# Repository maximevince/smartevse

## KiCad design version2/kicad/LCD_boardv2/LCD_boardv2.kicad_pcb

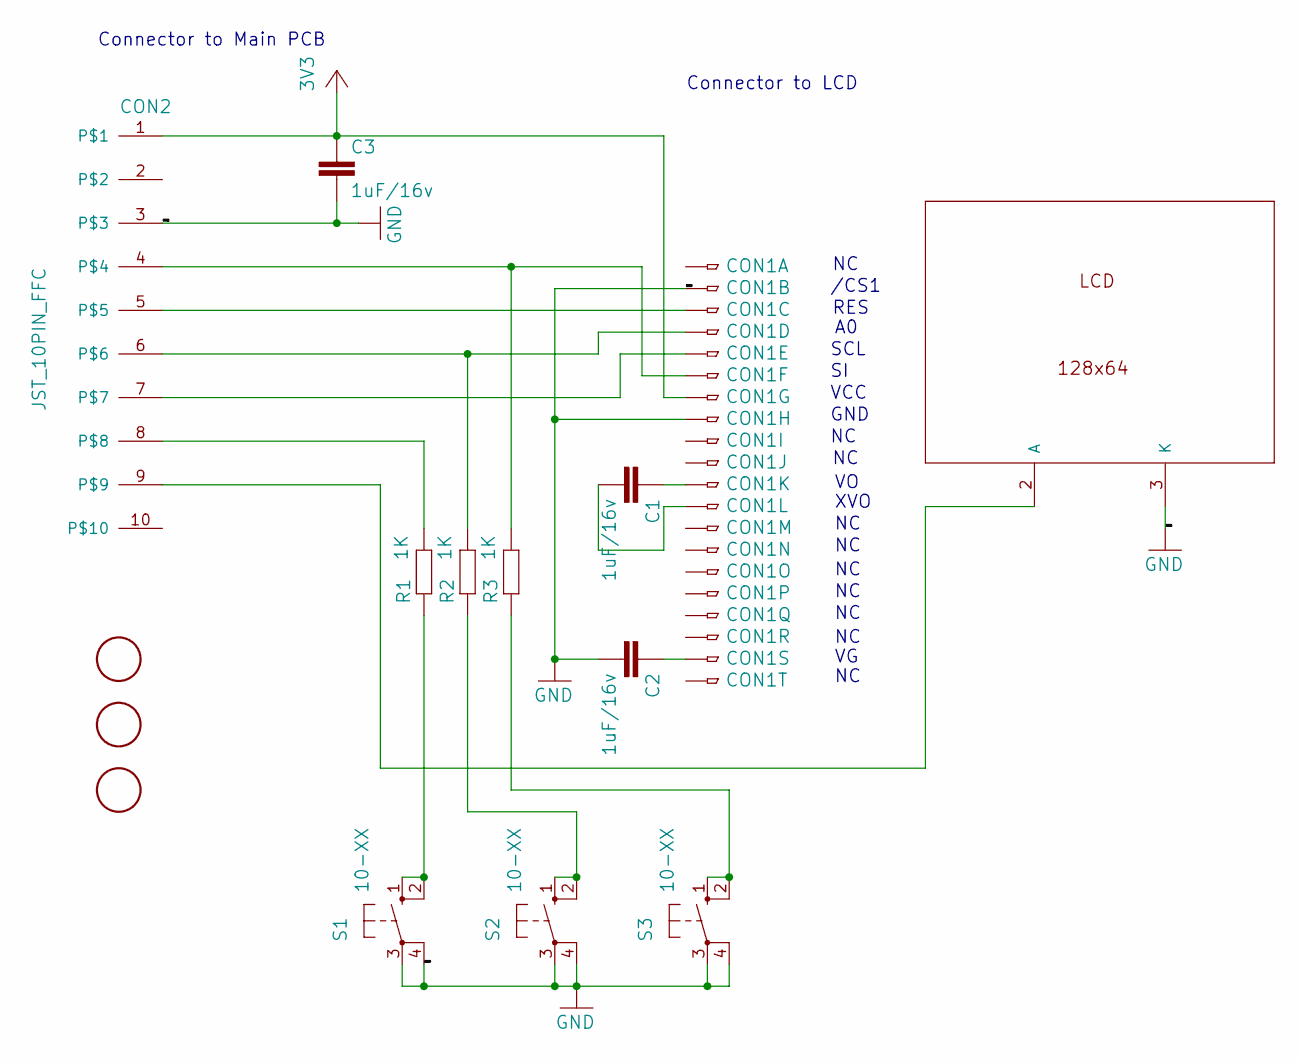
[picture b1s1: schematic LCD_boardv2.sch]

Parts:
C1, C2, C3: 1uF/16v; C0805
CON1: FH12-20S-0.5SH
CON2: JST_10PIN_FFC
R1, R2, R3: 1K; R0603
S1, S2, S3: 10-XX; B3F-10XX
U$1: LCD_DEM128064
U$2, U$3, U$4: FIDUCIAL; FIDUCIAL_1MM

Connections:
GND: C2.2, C3.2, CON1.2, CON1.8, CON2.3, S1.3, S1.4 (P1), S2.3, S2.4 (P1), S3.3, S3.4 (P1), U$1.3 (K)
unnamed: C1.1, CON1.11
unnamed: C1.2, CON1.12
unnamed: C2.1, CON1.19
unnamed: CON1.3, CON2.5
unnamed: CON1.4, CON2.6, R2.2
unnamed: CON1.5, CON2.7
unnamed: CON1.6, CON2.4, R3.2
unnamed: CON2.8, R1.2
unnamed: CON2.9, U$1.2 (A)
unnamed: R1.1, S1.1 (S), S1.2 (S1)
unnamed: R2.1, S2.1 (S), S2.2 (S1)
unnamed: R3.1, S3.1 (S), S3.2 (S1)
VCC: C3.1, CON1.7, CON2.1

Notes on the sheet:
/CS1
RES
SCL
VCC
GND
XVO
Connector to Main PCB
Connector to LCD

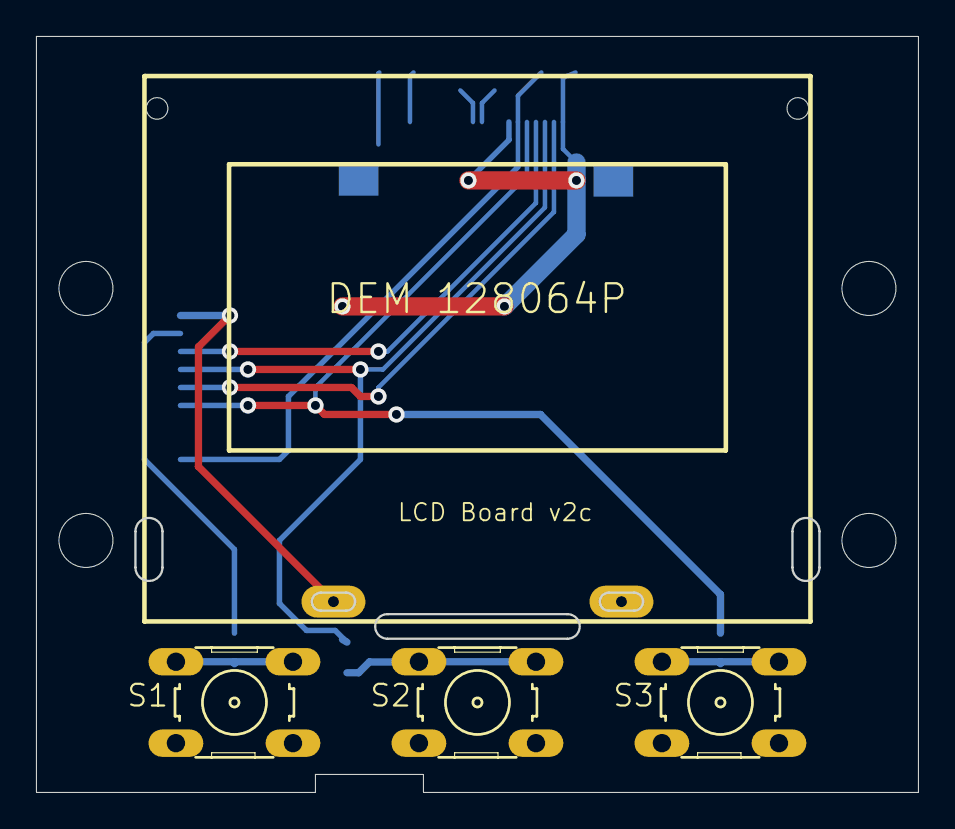
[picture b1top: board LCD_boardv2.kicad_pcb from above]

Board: 2 copper layers, 48.9 x 41.9 mm, 19 parts (0 on the bottom side), 14 nets.

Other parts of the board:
@HOLE0, @HOLE1, @HOLE2, @HOLE3: (no value)

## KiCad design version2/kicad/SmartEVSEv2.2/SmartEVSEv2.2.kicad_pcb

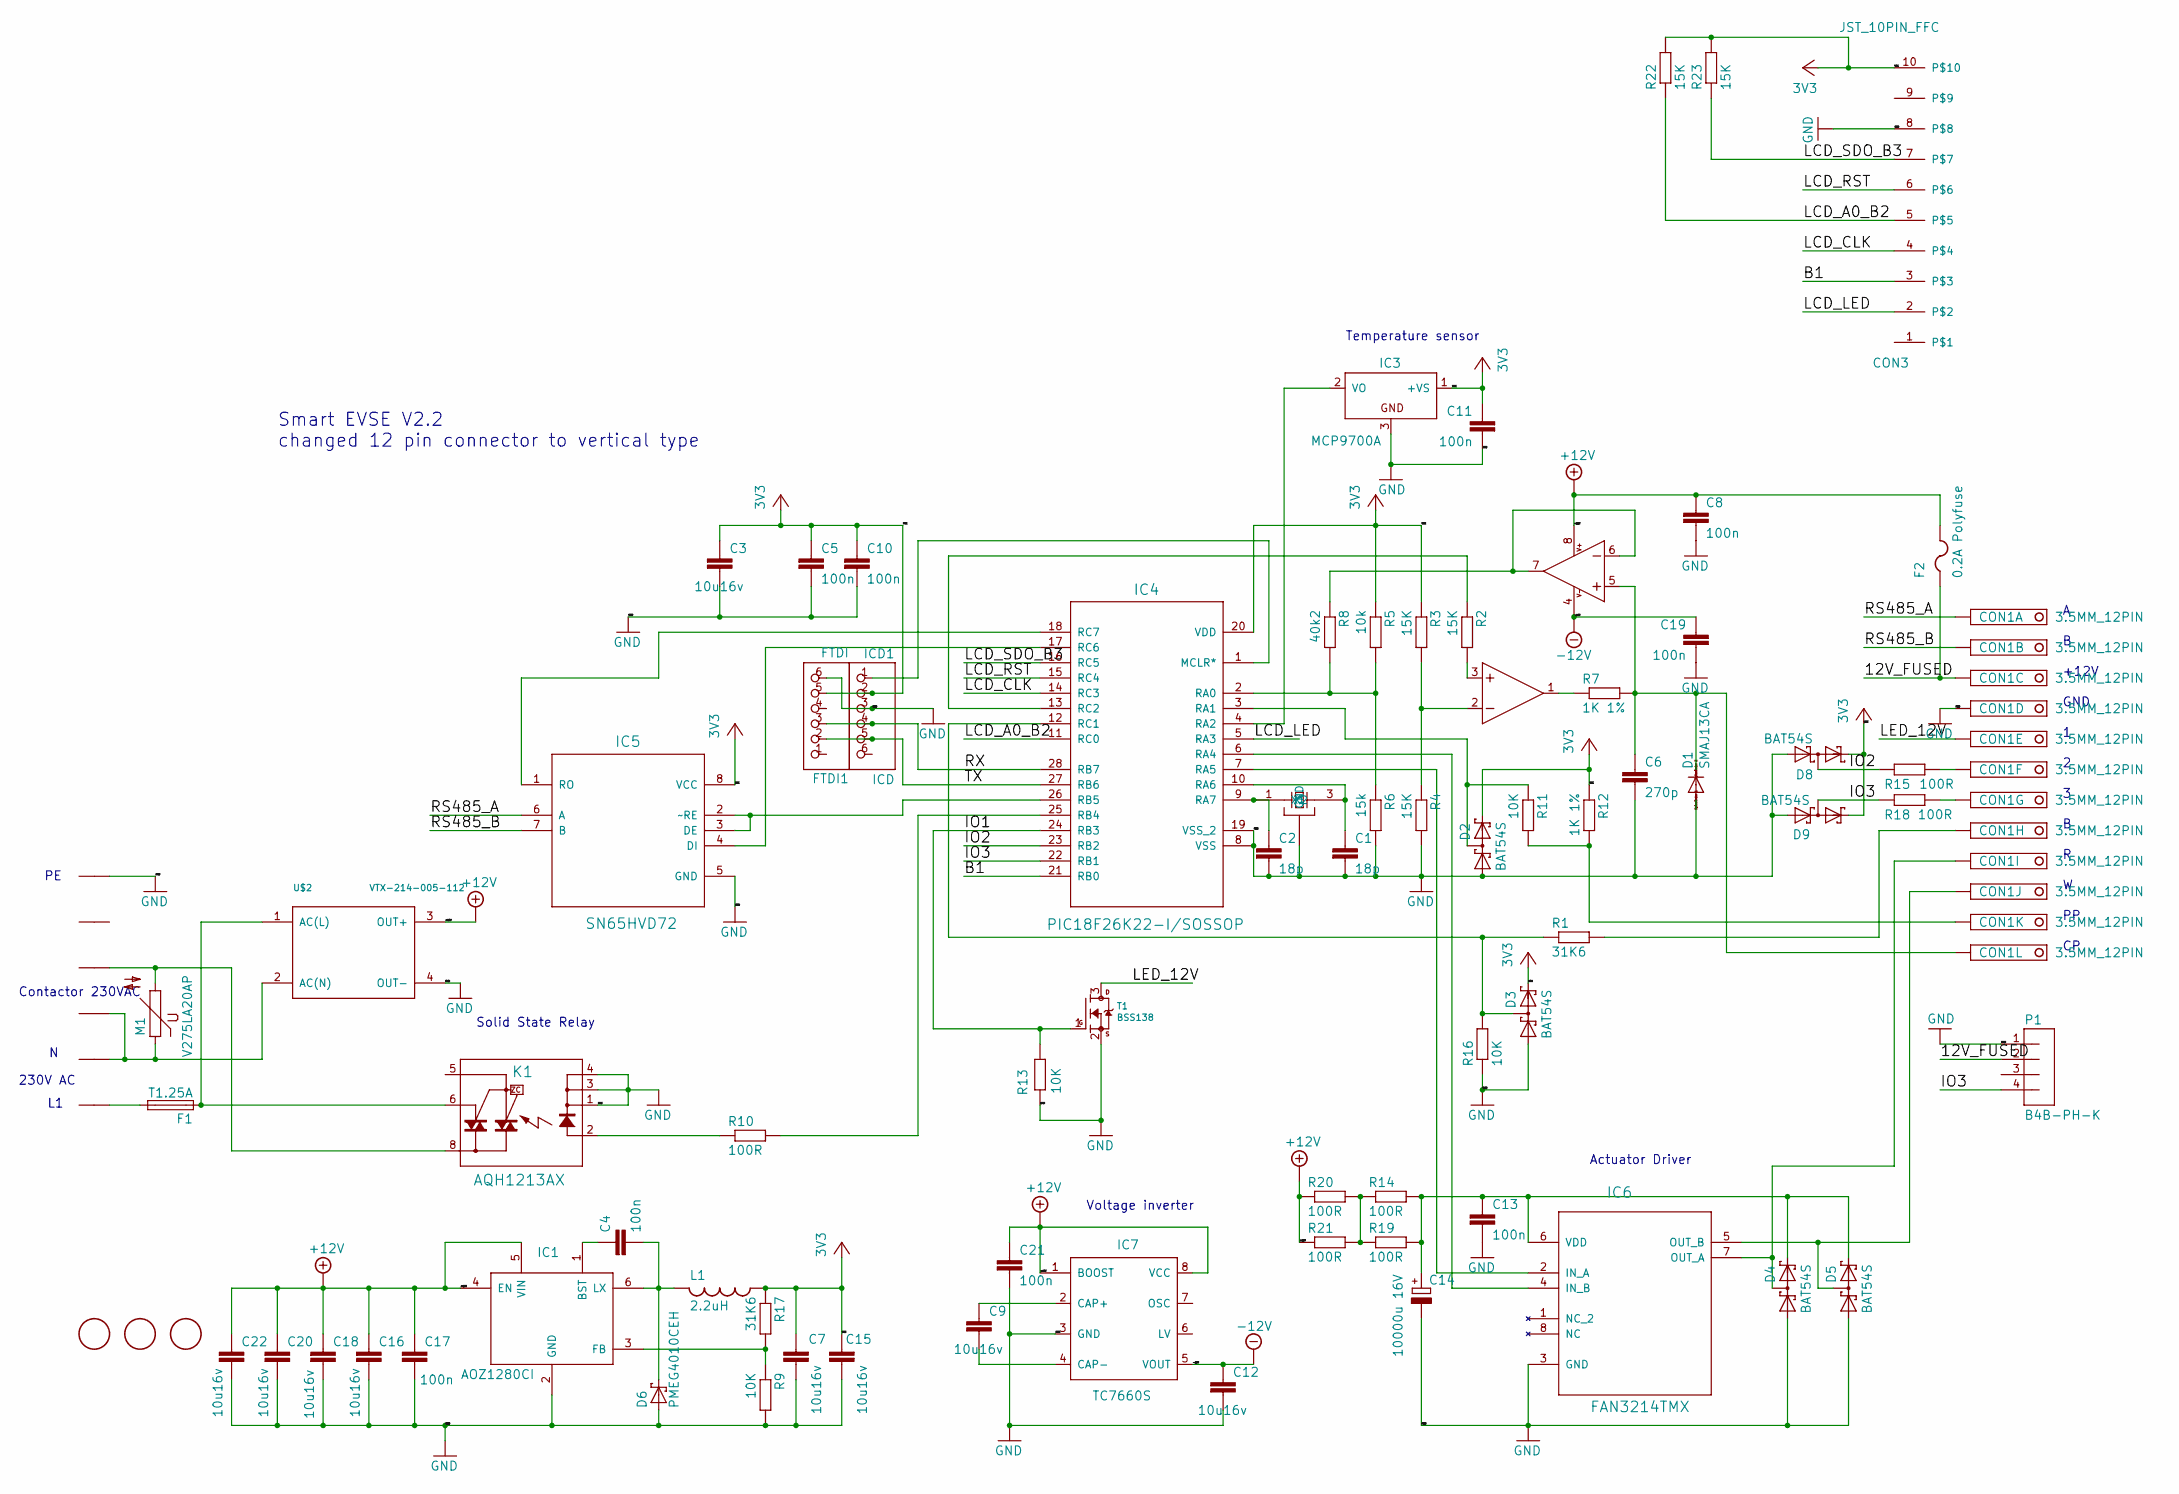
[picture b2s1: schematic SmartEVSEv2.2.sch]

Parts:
C1, C2: 18p; C0603
C3, C7, C9, C12, C15, C16, C18, C20, C22: 10u16v; C0805
C4, C5, C8, C10, C11, C13, C17, C19, C21: 100n; C0603
C6: 270p; C0805
C14: 10000u 16V; EB22,5D
CON1: 3.5MM_12PIN; 12PIN
CON2: DG128-7.5; P_AST027-06
CON3: JST_10PIN_FFC
D1: SMAJ13CA; DO214AC
D2, D3, D4, D5, D8, D9: BAT54S; SOT23
D6: PMEG4010CEH; SOD-123FL
F1: T1.25A; TE5
F2: 0.2A Polyfuse; R1210
FTDI1: FTDI; 1X06-BIGLOCK
IC1: AOZ1280CI; SOT23-6
IC2: LM7332MA; SO08
IC3: MCP9700A; SOT23
IC4: PIC18F26K22-I/SOSSOP; SOP65P780X200-28N
IC5: SN65HVD72; SOIC127P600X175-8N
IC6: FAN3214TMX; SOIC127P600X175-8N
IC7: TC7660S; SO08
ICD1: ICD; 1X06
K1: AQH1213AX; DIL07SMD
L1: 2.2uH; MCSD43
M1: V275LA20AP; S14K40
P1: B4B-PH-K
Q1: CTS_32X25_SMD; CTS_32X25
R1, R17: 31K6; R0603
R2, R3, R4, R22, R23: 15K; R0603
R5: 10k; R0603
R6: 15k; R0603
R7, R12: 1K 1%; R0603
R8: 40k2; R0603
R9, R11, R13, R16: 10K; R0603
R10, R14, R15, R18, R19, R20, R21: 100R; R0603
T1: BSS138; SOT23
U$1, U$3, U$4: FIDUCIAL; FIDUCIAL_1MM
U$2: VTX-214-005-112

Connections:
+12V: C8.1, C16.1, C17.1, C18.1, C20.1, C21.1, C22.1, F2.2, IC1.4 (EN), IC1.5 (VIN), IC2.8 (V+), IC7.1 (BOOST), IC7.8 (VCC), R20.1, R21.1, U$2.3 (OUT+)
-12V: C12.1, C19.1, IC2.4 (V-), IC7.5 (VOUT)
/12V_FUSED: CON1.3, F2.1, P1.2
/B1: CON3.3, IC4.21 (RB0)
/IO1: IC4.24 (RB3), R13.2, T1.1 (G)
/IO2: D8.3 (C1A2), IC4.23 (RB2), R15.1
/IO3: D9.3 (C1A2), IC4.22 (RB1), P1.4, R18.1
/LCD_A0_B2: CON3.5, IC4.11 (RC0), R22.1
/LCD_CLK: CON3.4, IC4.14 (RC3)
/LCD_LED: CON3.2, IC4.5 (RA3)
/LCD_RST: CON3.6, IC4.15 (RC4)
/LCD_SDO_B3: CON3.7, IC4.16 (RC5), R23.1
/LED_12V: CON1.5, T1.3 (D)
/RS485_A: CON1.1, IC5.6 (A)
/RS485_B: CON1.2, IC5.7 (B)
/RX: FTDI1.3, IC4.28 (RB7), ICD1.4
/TX: FTDI1.2, IC4.27 (RB6), ICD1.5
GND: C1.2, C2.2, C3.2, C5.2, C6.2, C7.1, C8.2, C10.2, C11.2, C12.2, C13.2, C14.-, C15.1, C16.2, C17.2, C18.2, C19.2, C20.2, C21.2, C22.2, CON1.4, CON2.P$6, CON3.8, D1.A, D2.1 (A1), D3.1 (A1), D4.1 (A1), D5.1 (A1), D6.A, D8.1 (A1), D9.1 (A1), FTDI1.6, IC1.2 (GND), IC3.3 (GND), IC4.8 (VSS), IC4.19 (VSS_2), IC5.5 (GND), IC6.3 (GND), IC7.3 (GND), ICD1.3, K1.1 (K), K1.3 (K1), K1.4 (K2), P1.1, Q1.2 (GND), Q1.4 (GND), R4.2, R6.2, R9.2, R13.1, R16.1, T1.2 (S), U$2.4 (OUT-)
unnamed: C1.1, IC4.10 (RA6), Q1.3 (X2)
unnamed: C2.1, IC4.9 (RA7), Q1.1 (X1)
unnamed: C4.1, IC1.1 (BST)
unnamed: C4.2, D6.C, IC1.6 (LX), L1.2
unnamed: C6.1, CON1.12, D1.C, IC2.5 (+IN), R7.2
unnamed: C9.1, IC7.2 (CAP+)
unnamed: C9.2, IC7.4 (CAP-)
unnamed: C13.1, C14.+, D4.2 (C2), D5.2 (C2), IC6.6 (VDD), R14.2, R19.2
unnamed: CON1.6, R15.2
unnamed: CON1.7, R18.2
unnamed: CON1.8, R1.2
unnamed: CON1.9, D4.3 (C1A2), IC6.7 (OUT_A)
unnamed: CON1.10, D5.3 (C1A2), IC6.5 (OUT_B)
unnamed: CON1.11, R11.2, R12.2
unnamed: CON2.P$1, F1.2
unnamed: CON2.P$2, CON2.P$3, M1.1, U$2.2 (AC(N))
unnamed: CON2.P$4, K1.8 (DS1), M1.2
unnamed: D2.3 (C1A2), IC4.3 (RA1), R11.1
unnamed: D3.3 (C1A2), IC4.12 (RC1), R1.1, R16.2
unnamed: F1.1, K1.6 (DS3), U$2.1 (AC(L))
unnamed: IC1.3 (FB), R9.1, R17.2
unnamed: IC2.1 (OUT), R7.1
unnamed: IC2.2 (-IN), R3.2, R4.1
unnamed: IC2.3 (+IN), R2.2
unnamed: IC2.6 (-IN), IC2.7 (OUT), R8.1
unnamed: IC3.2 (VO), IC4.4 (RA2)
unnamed: IC4.1 (MCLR*), ICD1.1
unnamed: IC4.2 (RA0), R5.2, R6.1, R8.2
unnamed: IC4.6 (RA4), IC6.4 (IN_B)
unnamed: IC4.7 (RA5), IC6.2 (IN_A)
unnamed: IC4.13 (RC2), R2.1
unnamed: IC4.17 (RC6), IC5.4 (DI)
unnamed: IC4.18 (RC7), IC5.1 (RO)
unnamed: IC4.25 (RB4), R10.2
unnamed: IC4.26 (RB5), IC5.2 (~~RE), IC5.3 (DE)
unnamed: K1.2 (A), R10.1
unnamed: R14.1, R19.1, R20.2, R21.2
VCC: C3.1, C5.1, C7.2, C10.1, C11.1, C15.2, CON3.10, D2.2 (C2), D3.2 (C2), D8.2 (C2), D9.2 (C2), FTDI1.5, IC3.1 (+VS), IC4.20 (VDD), IC5.8 (VCC), ICD1.2, L1.1, R3.1, R5.1, R12.1, R17.1, R22.2, R23.2

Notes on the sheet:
230V AC
Contactor 230VAC
Smart EVSE V2.2 changed 12 pin connector to vertical type
Temperature sensor
Actuator Driver
Solid State Relay
Voltage inverter
GND
+12V

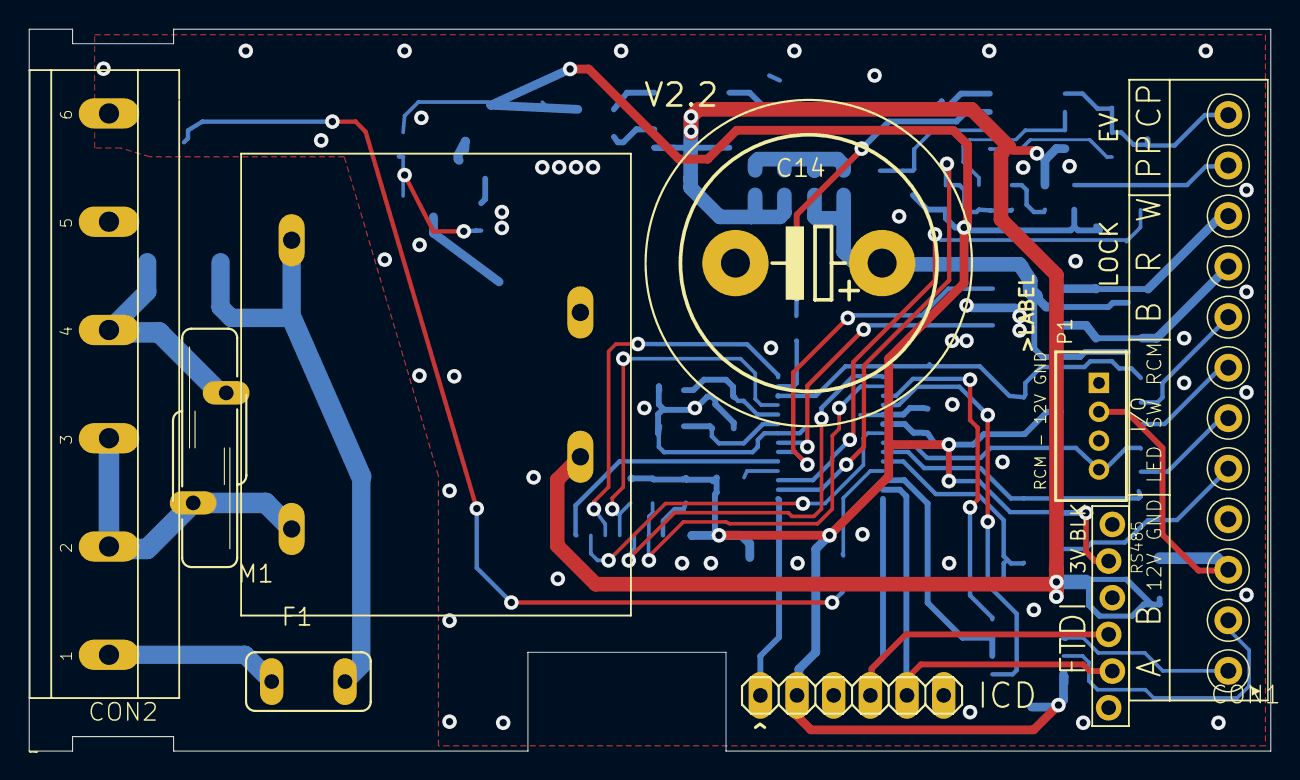
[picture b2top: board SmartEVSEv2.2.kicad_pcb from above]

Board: 2 copper layers, 86.0 x 50.0 mm, 77 parts (0 on the bottom side), 56 nets.

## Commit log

2019-11-28 Move version1 to separate directory
2019-11-28 Add Kicad EDA files (imported from Eagle)
2019-11-29 Add Kicad EDA files (imported from Eagle) (2)
2019-11-29 Some basic refactoring, using fixed-width datatypes, enums, ...
